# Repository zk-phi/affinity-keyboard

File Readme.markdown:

# AFFINITY Keyboard

※試作品です (TODO 参照)

7 バンドスペアナ IC を搭載し、音声入力に応じて LED のパターンを変化させるなどのギミックを実装できるサブキーボードです。

TRRS ジャックが２つ生えているので、片方に音楽プレーヤーなどの出力を、他方にイヤホンなどを接続して使用します。

MX スイッチ、 Choc スイッチに対応しています。

## 動画

レベルメーター風

- https://twitter.com/zk_phi/status/1271797216508669954

パリピモード (ビートに合わせて演出)

- https://twitter.com/zk_phi/status/1272497990968565760

## パーツ

- メイン基板
- ボトムプレート
- ProMicro カバー
- いつもの
  - ダイオード 1N4148w x16
  - 2 ピンタクトスイッチ x1
  - コンスルー付き ProMicro x1
- LED
  - SK6812mini x16
  - チップコンデンサ 0.1uF (2012 Metrics) x16
- スペアナ周辺回路
  - スペアナ IC MSGEQ7 x1
  - チップコンデンサ 0.1uF (2012 Metrics) x3
  - コンデンサ 33pF (2.5mm ピッチ) x1
  - チップ抵抗 220K (2012 Metrics) x1
  - チップ抵抗 22K (2012 Metrics) x2
  - TRRS ジャック MJ-4PP-9 x2
- キースイッチ
  - 5-pin MX 互換 or Choc x16
    - 初期の Choc クリッキーにあった追加のピンは刺さりません
- ネジ類
  - M2 スペーサ 5mm x5
  - M2 スペーサ 7mm x2
    - コンスルーの足を切れば 5mm でも ok (その方が個人的には好き)
  - M2 ネジ 3~4mm x14
  - ゴム足 4 個

### 入手先の例

- スペアナ IC

http://akizukidenshi.com/catalog/g/gI-12887/

- チップコンデンサ

http://akizukidenshi.com/catalog/g/gP-14572/

- コンデンサ

http://akizukidenshi.com/catalog/g/gP-13317/

- チップ抵抗

https://www.sengoku.co.jp/mod/sgk_cart/detail.php?code=EEHD-57CU (220K)

https://www.sengoku.co.jp/mod/sgk_cart/detail.php?code=EEHD-57CG (22K)

## TODO

今のバージョンにはいくつか改善の余地があります。

### 凡ミス系

- PCB マウントのピンが若干ゆるく、 choc スイッチの位置決めがやや難しい
  - 個体差かも？

- ２つの TRRS ジャックの間が思ったより狭く、太いプラグは２本刺さらない
  - 写真参照

- Pro Micro カバーをつけてしまうとリセットスイッチが押せない (!!)
  - キーの組み合わせでリセットをかけられるようにして対応

### 音量調節問題

どれくらいの音量に反応させるかはファームウェア側でも設定できますが、とはいえ入力が小さいと精度がかなり落ちます。そのため、キーボードに入力する音声は一般的なポータブルプレーヤーの MAX 近い音量が推奨になります (「レベルメーター」モードで、一番上の行がたまーに光るくらい)。

実用するには、

```
プレーヤー
| (音量大)
このキーボード
|
減衰器
| (音量小)
イヤホン
```

のようにイヤホンへの入力だけを減衰するか、逆に

```
プレーヤー
|
+-- アンプ --- (音量大) このキーボード
|
+-- (音量小) イヤホン
```

のようにこのキーボードへの入力だけを増幅する感じになると思います。

減衰器は適当な (どれくらい減衰させたいかによる) 大きさの抵抗を探してくるだけで簡単に作れるほか、市販でも「抵抗入りケーブル」「ボリューム付きケーブル」などの名前で売られています。

私は以下のような回路をブレッドボードに仮組みして使っています。

```
Keyboard         ->         Earphone

Lout --- 30 Ohm ---+------- Lin
                   |
                 10 Ohm
                   |
Rout --- 30 Ohm ---|---+--- Rin
                   |   |
                   | 10 Ohm
                   |   |
 GND --------------+---+--- GND
```

詳しいことはわかりませんが、普通のカーボン抵抗よりも金属皮膜抵抗の方が音質がよかったです (特に 30 Ohm の方)。

ゆくゆくはこのキーボードに簡単なアンプ回路を内蔵するべきなのかなあと思っています。

### ノイズ問題

LED がたくさん光っていると、音声に謎のノイズが乗ります。

現状では LED をノイズが気にならない程度の光量に抑えて対応しています。

今までにわかっていること：

- 以前近いコンセプトの試作品を作った時は LED にパスコンがなかったのでパスコンをつけた、マシにはなったのかもしれない (?) けど解決にはならず
- 相手のデバイス (オーディオプレーヤーなど) と繋いでいる時だけ問題の音が出ることを確認
- LED 光らせている時だけ問題の音が出ることを確認
- イヤホン出力の GND やオーディオ入力の GND にフェライトビーズを挟んで無理やり分離しようとしてみたが解決にはならず

フィードバック・アドバイス・プルリク歓迎です。むしろ誰か助けて。

----

追記

- PC からではなく別電源から給電するとノイズが乗らないことがわかったので、単純に電源のパワーが足りないだけの可能性が出てきました

----

追記２

- 電源と音声を両方とも PC から入力した場合だけ不安定になることがわかってきました。キーボードは PC に接続しつつ、音声は別のプレーヤー入力すると問題なさそうです

## 組み立て

- 裏面に実装する表面実装部品 (ダイオード、チップコンデンサ、 LED) を実装します
  - チップコンを最初につけるのが個人的にはらくでした
  - ダイオードはコの字の印がカソード、 LED はコの字の印が Vcc です
  - LED の実装順は最上段の Pro Micro 側から反対側へ (写真では左から右)
  - ２段目以降も同様

- ファームを焼いた Pro Micro をコンスルーで差し込み動作テストをします
  - LED のテストには Helix の `led_test` キーマップが便利です (`make helix/rev2:led_test:avrdude`)
    - (音を検知しないと光らないので)
  - このキーボードのキーマップは `zk-phi/qmk_firmware` にあります: `make handwired/affinity:default:avrdude`

- おもて面に実装する部品を背の低いものから実装します
  - チップ抵抗、チップコンデンサ、スペアナ IC、リセットスイッチ、コンデンサ、 TRRS ジャック

- キースイッチを実装します

- ボトムプレートに５つ、メイン基板に２つスペーサーを立てます

- ボトムプレートにメイン基板を取り付け、メイン基板に Pro Micro カバーを取り付けます
  - この順でないと取り付けられません (これも要改善かも)

- ゴム足を貼れば完成

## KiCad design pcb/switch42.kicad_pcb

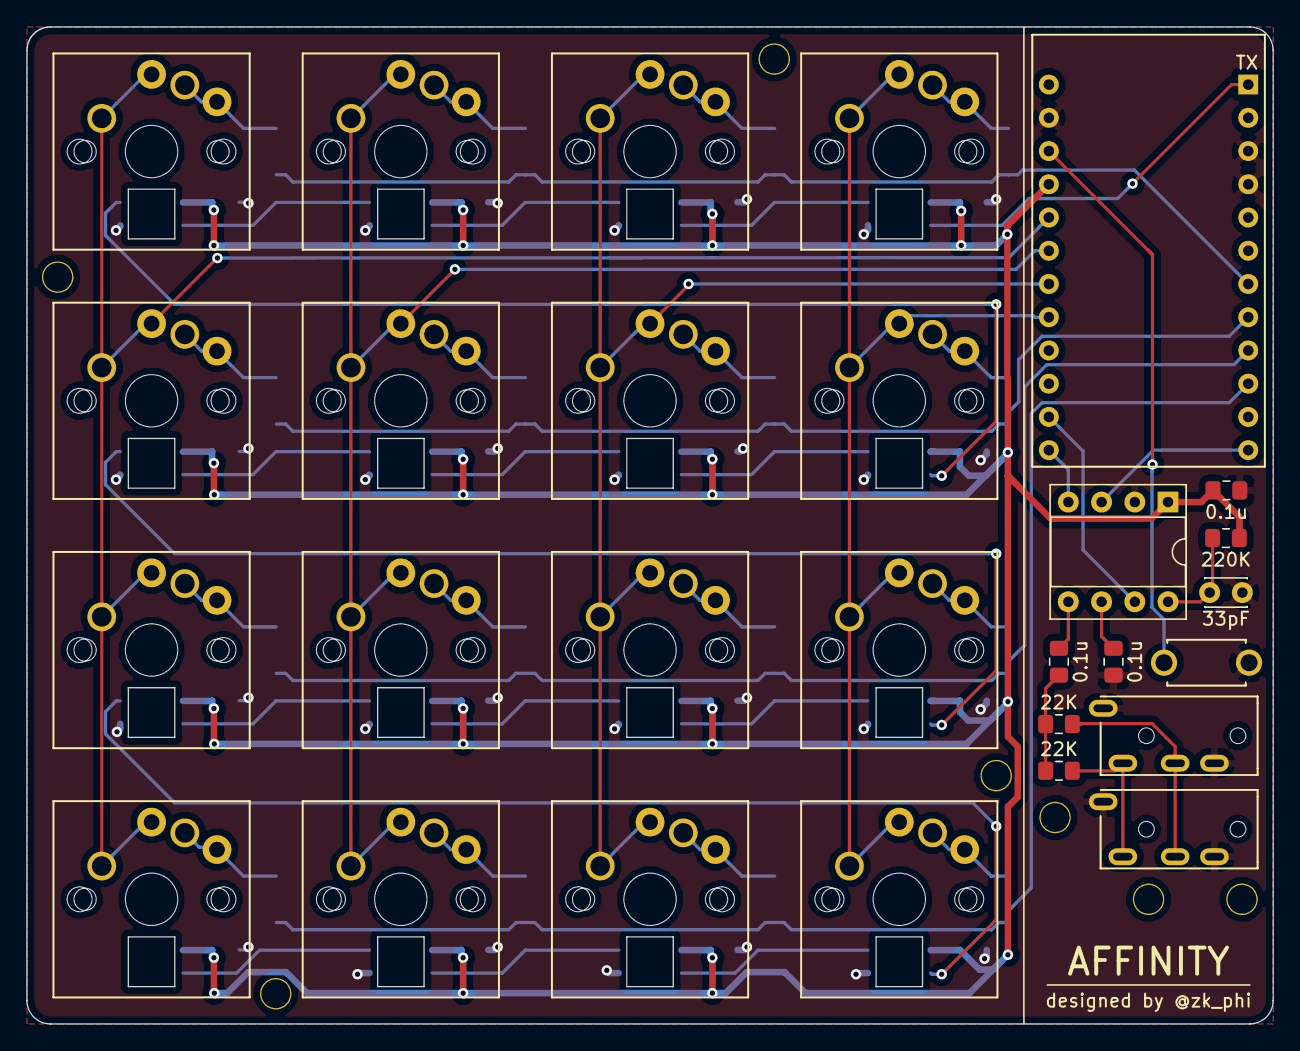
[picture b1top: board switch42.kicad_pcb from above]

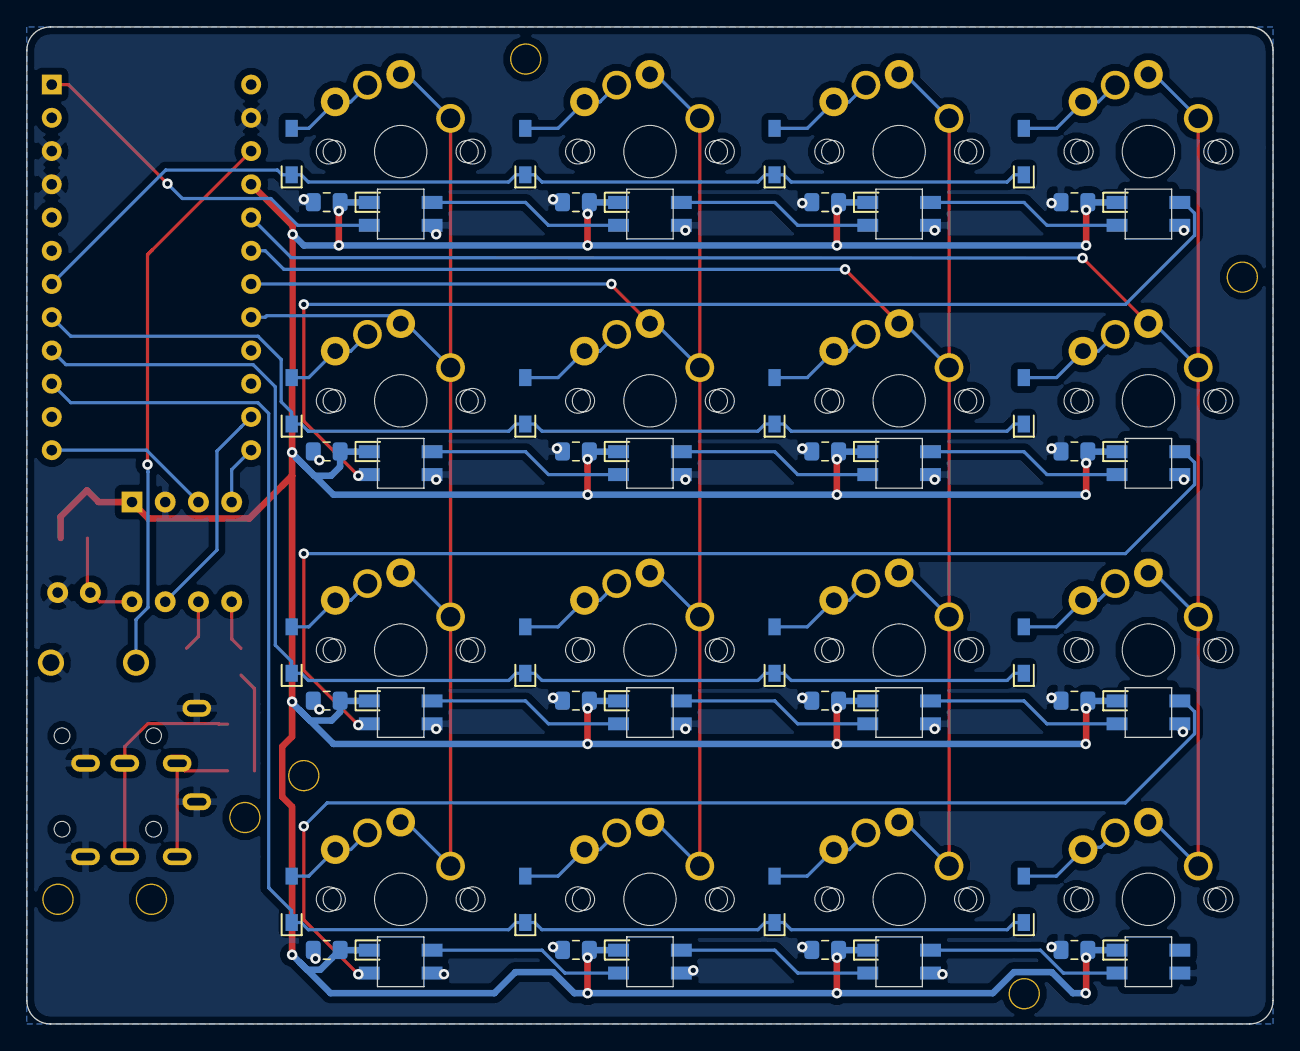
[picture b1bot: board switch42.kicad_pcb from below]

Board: 2 copper layers, 95.2 x 76.2 mm, 83 parts (32 on the bottom side), 52 nets.

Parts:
0.1u, 0.1u#2, 0.1u#3: C_Small; C_0805_2012Metric_Pad1.15x1.40mm_HandSolder
22K, 22K#2, 220K: R_Small; R_0805_2012Metric_Pad1.15x1.40mm_HandSolder
33pF: C_Small; Capacitor_Disc_2.50mm-irreversible
C5, C6, C7, C8, C11, C12, C13, C14, C17, C18, C19, C20, C24, C25, C26, C27: C_Small; C_0805_2012Metric_Pad1.15x1.40mm_HandSolder
D1, D2, D3, D4, D6, D7, D8, D9, D11, D12, D13, D14, D16, D17, D18, D19: D; D_SMD-irreversible
J1, J2: MJ-4PP-9; MJ-4PP-9-irreversible
L1, L2, L3, L4, L6, L7, L8, L9, L11, L12, L13, L14, L16, L17, L18, L19: SK6812MINI; SK6812MINI_narrow-irreversible
Ref**: Val**; M2_SCREW_HOLE
Ref**#2, Ref**#3, Ref**#4, Ref**#5, Ref**#6, Ref**#7: Val**; M2_SCREW_HOLE
SW1: SW_PUSH; ResetSW-irreversible
SW2, SW3, SW4, SW5, SW7, SW8, SW9, SW10, SW12, SW13, SW14, SW15, SW17, SW18, SW19, SW20: SW_PUSH; MX_or_Choc_1.00u-irreversible
U1: ProMicro; ProMicro_Reversed_Conthrough-irreversible
U2: MSGEQ7; DIP-8_W7.62mm_Socket

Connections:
AIN: 0.1u#2.1, U2.5
EQOUT: U1.12, U2.3
EQRST: U1.14, U2.7
GND: 0.1u.1, 0.1u#3.2, 33pF.1, C5.1, C6.1, C7.1, C8.1, C11.2, C12.2, C13.2, C14.2, C17.1, C18.1, C19.1, C20.1, C24.2, C25.2, C26.2, C27.2, J1.A, J1.B, J2.A, J2.B, L1.2, L2.2, L3.2, L4.2, L6.2, L7.2, L8.2, L9.2, L11.2, L12.2, L13.2, L14.2, L16.2, L17.2, L18.2, L19.2, SW1.2, U1.3, U1.4, U1.23, U2.2
unnamed: 33pF.2, 220K.2, U2.8
unnamed: 0.1u.2, U2.6
unnamed: 0.1u#2.2, 22K.1, 22K#2.1
unnamed: D1.2, SW2.2
unnamed: D2.2, SW3.2
unnamed: D3.2, SW4.2
unnamed: D4.2, SW5.2
unnamed: D6.2, SW7.2
unnamed: D7.2, SW8.2
unnamed: D8.2, SW9.2
unnamed: D9.2, SW10.2
unnamed: D11.2, SW12.2
unnamed: D12.2, SW13.2
unnamed: D13.2, SW14.2
unnamed: D14.2, SW15.2
unnamed: D16.2, SW17.2
unnamed: D17.2, SW18.2
unnamed: D18.2, SW19.2
unnamed: D19.2, SW20.2
unnamed: 22K#2.2, J1.C, J2.C
unnamed: 22K.2, J1.D, J2.D
unnamed: L1.1, L6.3
unnamed: L2.1, L7.3
unnamed: L3.1, L8.3
unnamed: L4.1, L9.3
unnamed: L11.1, L16.3
unnamed: L6.1, L11.3
unnamed: L12.1, L17.3
unnamed: L7.1, L12.3
unnamed: L13.1, L18.3
unnamed: L8.1, L13.3
unnamed: L14.1, L19.3
unnamed: L9.1, L14.3
unnamed: L2.3, L16.1
unnamed: L3.3, L17.1
unnamed: L4.3, L18.1
STROBE: U1.13, U2.4
VCC: 0.1u#3.1, 220K.1, C5.2, C6.2, C7.2, C8.2, C11.1, C12.1, C13.1, C14.1, C17.2, C18.2, C19.2, C20.2, C24.1, C25.1, C26.1, C27.1, L1.4, L2.4, L3.4, L4.4, L6.4, L7.4, L8.4, L9.4, L11.4, L12.4, L13.4, L14.4, L16.4, L17.4, L18.4, L19.4, U1.21, U2.1
col0: SW2.1, SW3.1, SW4.1, SW5.1, U1.20
col1: SW7.1, SW8.1, SW9.1, SW10.1, U1.19
col2: SW12.1, SW13.1, SW14.1, SW15.1, U1.18
col3: SW17.1, SW18.1, SW19.1, SW20.1, U1.17
led: L1.3, U1.1
reset: SW1.1, U1.22
row0: D1.1, D6.1, D11.1, D16.1, U1.7
row1: D2.1, D7.1, D12.1, D17.1, U1.8
row2: D3.1, D8.1, D13.1, D18.1, U1.9
row3: D4.1, D9.1, D14.1, D19.1, U1.10

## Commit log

2020-06-15 Add Readme
2020-06-15 Add doc: LED direction
2020-06-15 Add party people
2020-06-15 Fix doc
2020-06-15 Fix schematic
2020-06-15 Update build guide
2020-06-15 Fix part no
2020-06-15 Update doc
2020-06-17 Add License
2020-06-18 Add shopping info
2020-06-19 Add doc
